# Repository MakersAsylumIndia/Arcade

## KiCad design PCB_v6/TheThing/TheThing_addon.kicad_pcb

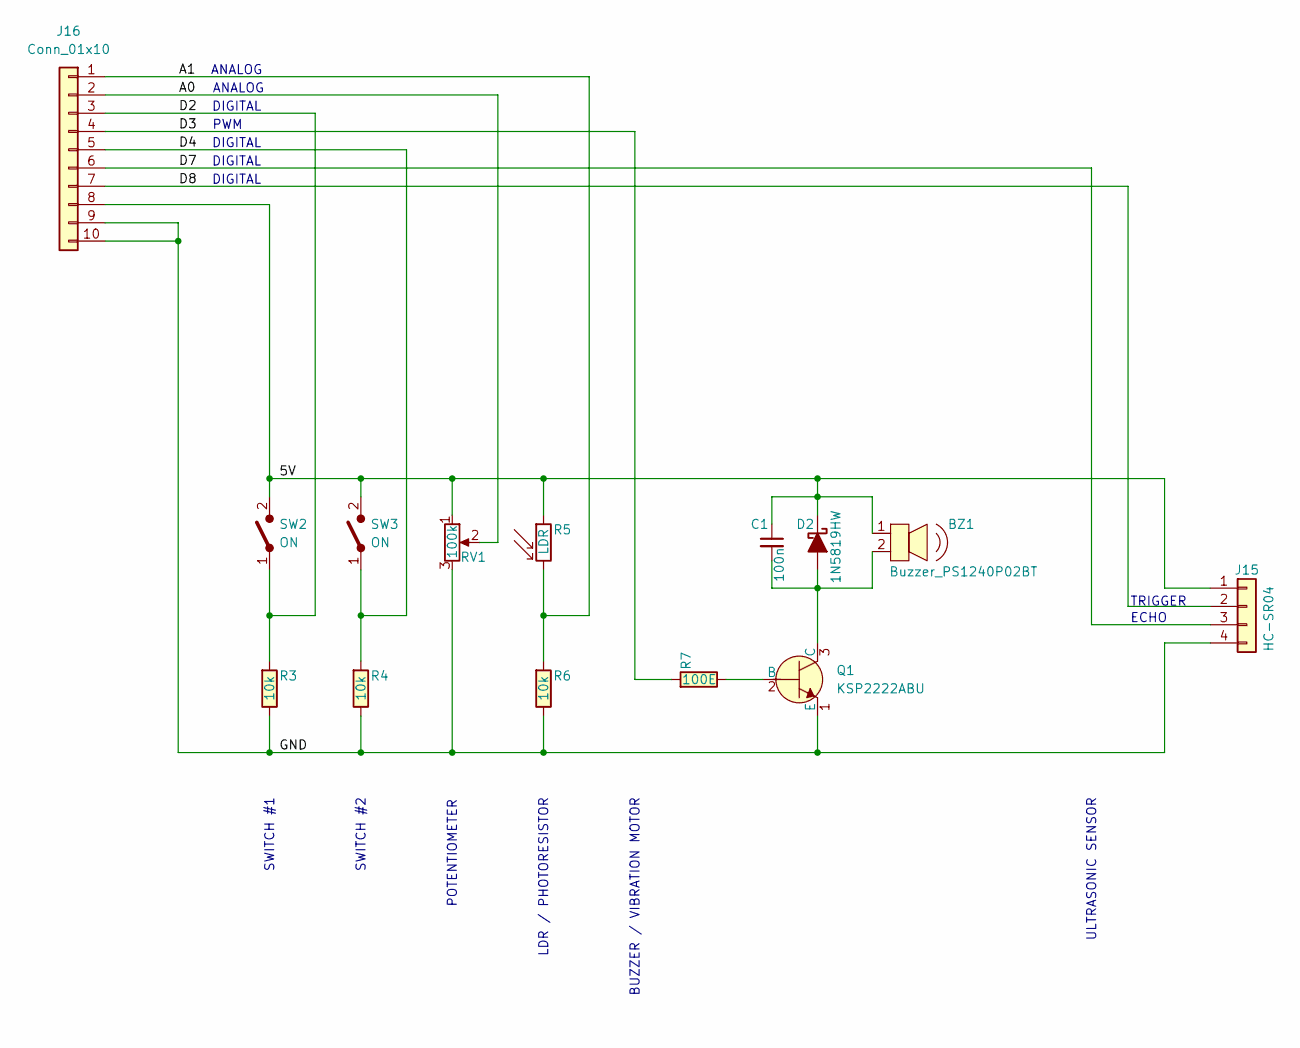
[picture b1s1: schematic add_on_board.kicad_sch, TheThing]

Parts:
BZ1: Buzzer_PS1240P02BT; Buzzer_12x9.5RM7.6; MPN PS1240P02BT; Digi-Key_PN 445-2525-1-ND
C1: 100n; C_Disc_D3.0mm_W2.0mm_P2.50mm
D2: 1N5819HW; D_DO-41_SOD81_P10.16mm_Horizontal
J15: HC-SR04; PinSocket_1x04_P2.54mm_Vertical
J16: Conn_01x10; PinHeader_1x10_P2.54mm_Vertical
Q1: KSP2222ABU; TO-92_HandSolder; MPN KSP2222ABU; Digi-Key_PN KSP2222ABUFS-ND
R3, R4, R6: 10k; R_Axial_DIN0207_L6.3mm_D2.5mm_P7.62mm_Horizontal
R5: LDR; R_LDR_4.9x4.2mm_P2.54mm_Vertical
R7: 100E; R_Axial_DIN0207_L6.3mm_D2.5mm_P7.62mm_Horizontal
RV1: 100k; TRIM_3352T-1-253LF
SW2, SW3: ON; SWITCH_PUSH_6mm_12mm

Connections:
/Add_on_Board/5V: BZ1.1, C1.1, D2.1 (K), J15.1, J16.8, R5.1, RV1.1, SW2.2 (B), SW3.2 (B)
/Add_on_Board/A0: J16.2, RV1.2
/Add_on_Board/A1: J16.1, R5.2, R6.1
/Add_on_Board/D2: J16.3, R3.1, SW2.1 (A)
/Add_on_Board/D3: J16.4, R7.1
/Add_on_Board/D4: J16.5, R4.1, SW3.1 (A)
/Add_on_Board/D7: J15.3, J16.6
/Add_on_Board/D8: J15.2, J16.7
/Add_on_Board/GND: J15.4, J16.9, J16.10, Q1.1 (E), R3.2, R4.2, R6.2, RV1.3
unnamed: BZ1.2, C1.2, D2.2 (A), Q1.3 (C)
unnamed: Q1.2 (B), R7.2

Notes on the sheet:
SWITCH #1
BUZZER / VIBRATION MOTOR
SWITCH #2
ULTRASONIC SENSOR
ANALOG
DIGITAL
PWM
LDR / PHOTORESISTOR
ECHO
TRIGGER
POTENTIOMETER

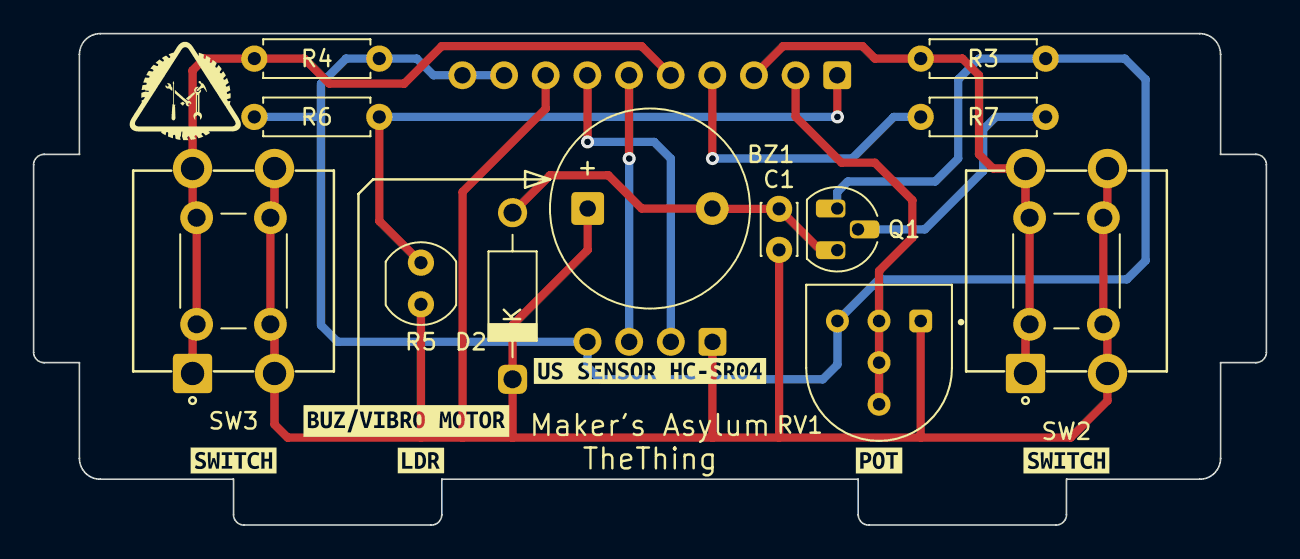
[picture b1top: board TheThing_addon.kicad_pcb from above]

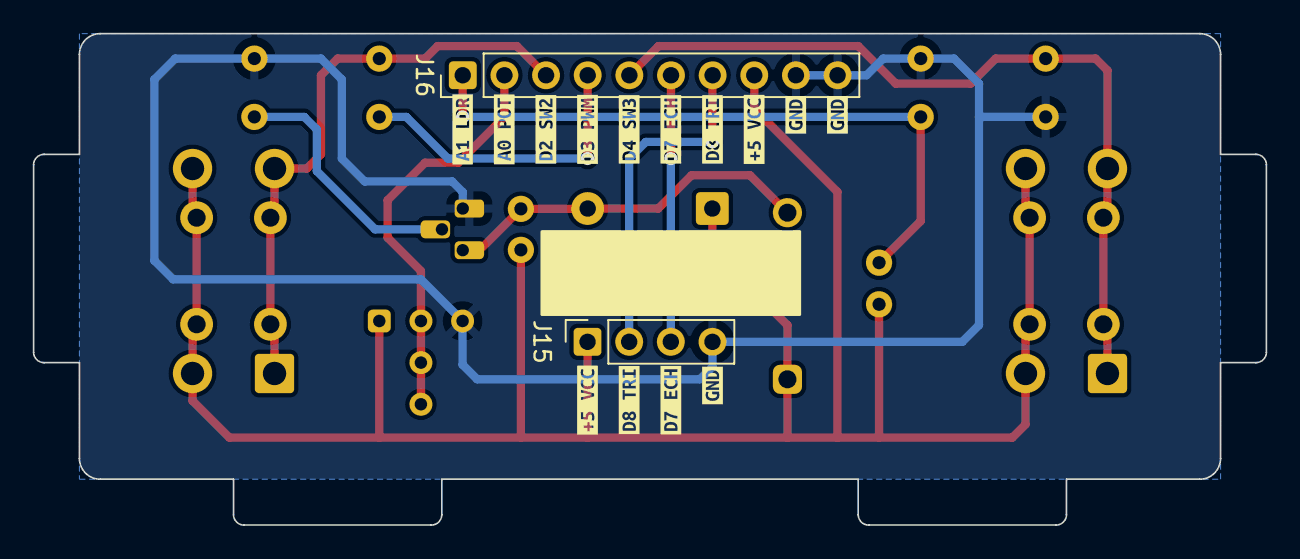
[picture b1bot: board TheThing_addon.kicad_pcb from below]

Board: 2 copper layers, 75.2 x 30.0 mm, 34 parts (16 on the bottom side), 11 nets.

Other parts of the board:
kibuzzard-67A11ADA: G***; kibuzzard-67A11ADA
kibuzzard-67A22DCA: G***; kibuzzard-67A22DCA
kibuzzard-67A22DD3: G***; kibuzzard-67A22DD3
kibuzzard-67A22DDD: G***; kibuzzard-67A22DDD
kibuzzard-67A22DE4: G***; kibuzzard-67A22DE4
kibuzzard-67A22DF7: G***; kibuzzard-67A22DF7
kibuzzard-67A22E24: G***; kibuzzard-67A22E24
kibuzzard-67A121CB: G***; kibuzzard-67A121CB
kibuzzard-67A121DF: G***; kibuzzard-67A121DF
kibuzzard-67A121F4: G***; kibuzzard-67A121F4
kibuzzard-67A122A3, kibuzzard-67A122A3#2: G***; kibuzzard-67A122A3
kibuzzard-67A122B8: G***; kibuzzard-67A122B8
kibuzzard-67A122C1, kibuzzard-67A122C1#2: G***; kibuzzard-67A122C1
kibuzzard-67A201C7: G***; kibuzzard-67A201C7
kibuzzard-67A201D4: G***; kibuzzard-67A201D4
kibuzzard-67A1228F: G***; kibuzzard-67A1228F
kibuzzard-67A12228: G***; kibuzzard-67A12228
kibuzzard-67A12264: G***; kibuzzard-67A12264

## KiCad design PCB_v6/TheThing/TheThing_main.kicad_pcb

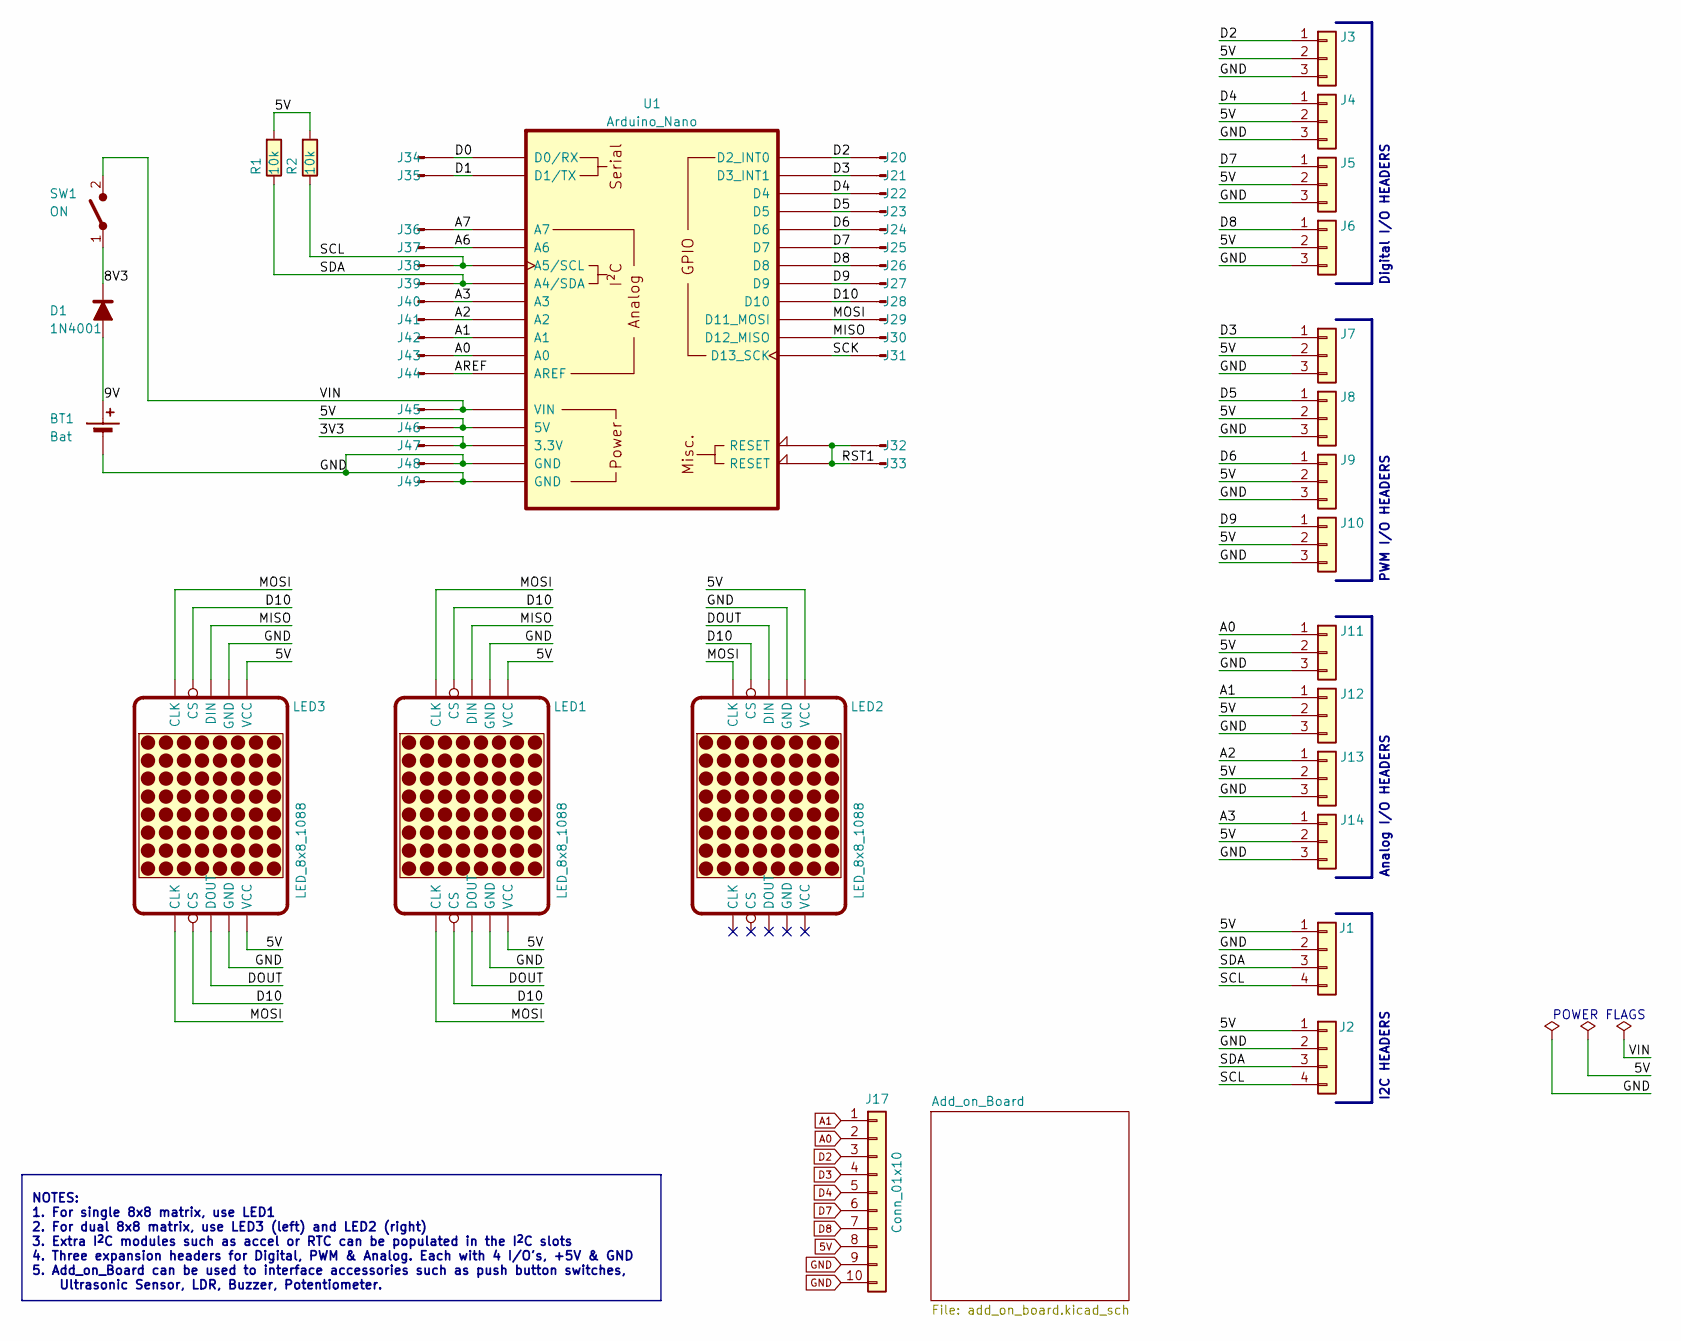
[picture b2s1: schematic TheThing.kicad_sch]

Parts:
BT1: Bat; PinHeader_1x02_P2.54mm_Vertical
D1: 1N4001; D_DO-41_SOD81_P10.16mm_Horizontal
J1, J2: Conn_I2C; PinHeader_1x04_P2.54mm_Vertical
J3, J4, J5, J6, J7, J8, J9, J10, J11, J12, J13, J14: Conn_01x03; PinHeader_1x03_P2.54mm_Vertical
J17: Conn_01x10; PinHeader_1x10_P2.54mm_Vertical
J20: D2; PinHeader_1x01_P2.54mm_Vertical
J21: D3; PinHeader_1x01_P2.54mm_Vertical
J22: D4; PinHeader_1x01_P2.54mm_Vertical
J23: D5; PinHeader_1x01_P2.54mm_Vertical
J24: D6; PinHeader_1x01_P2.54mm_Vertical
J25: D7; PinHeader_1x01_P2.54mm_Vertical
J26: D8; PinHeader_1x01_P2.54mm_Vertical
J27: D9; PinHeader_1x01_P2.54mm_Vertical
J28: D10; PinHeader_1x01_P2.54mm_Vertical
J29: D11; PinHeader_1x01_P2.54mm_Vertical
J30: D12; PinHeader_1x01_P2.54mm_Vertical
J31: D13; PinHeader_1x01_P2.54mm_Vertical
J32, J33: RST1; PinHeader_1x01_P2.54mm_Vertical
J34: D0; PinHeader_1x01_P2.54mm_Vertical
J35: D1; PinHeader_1x01_P2.54mm_Vertical
J36: A7; PinHeader_1x01_P2.54mm_Vertical
J37: A6; PinHeader_1x01_P2.54mm_Vertical
J38: A5; PinHeader_1x01_P2.54mm_Vertical
J39: A4; PinHeader_1x01_P2.54mm_Vertical
J40: A3; PinHeader_1x01_P2.54mm_Vertical
J41: A2; PinHeader_1x01_P2.54mm_Vertical
J42: A1; PinHeader_1x01_P2.54mm_Vertical
J43: A0; PinHeader_1x01_P2.54mm_Vertical
J44: AREF; PinHeader_1x01_P2.54mm_Vertical
J45: VIN; PinHeader_1x01_P2.54mm_Vertical
J46: 5V; PinHeader_1x01_P2.54mm_Vertical
J47: 3V3; PinHeader_1x01_P2.54mm_Vertical
J48: GND1; PinHeader_1x01_P2.54mm_Vertical
J49: GND2; PinHeader_1x01_P2.54mm_Vertical
LED1, LED2, LED3: LED_8x8_1088; LED_matrix_8x8_M1088
R1, R2: 10k; R_Axial_DIN0207_L6.3mm_D2.5mm_P7.62mm_Horizontal
SW1: ON; SW_CuK_OS102011MA1QN1_SPDT_Angled
U1: Arduino_Nano; Arduino_Nano_v2_NoSPI

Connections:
5V: J1.1, J2.1, J3.2, J4.2, J5.2, J6.2, J7.2, J8.2, J9.2, J10.2, J11.2, J12.2, J13.2, J14.2, J17.8, J46.1, LED1.VCC1 (VCC), LED1.VCC2 (VCC), LED2.VCC1 (VCC), LED3.VCC1 (VCC), LED3.VCC2 (VCC), R1.1, R2.1, U1.5V
/3V3: J47.1, U1.3V3 (3.3V)
/8V3: D1.1 (K), SW1.1 (A)
/9V: BT1.1 (+), D1.2 (A)
/A2: J13.1, J41.1, U1.A2
/A3: J14.1, J40.1, U1.A3
/A6: J37.1, U1.A6
/A7: J36.1, U1.A7
/AREF: J44.1, U1.AREF
/D0: J34.1, U1.D0 (D0/RX)
/D1: J35.1, U1.D1 (D1/TX)
/D5: J8.1, J23.1, U1.D5
/D6: J9.1, J24.1, U1.D6
/D9: J10.1, J27.1, U1.D9
/D10: J28.1, LED1.CS1 (CS), LED1.CS2 (CS), LED2.CS1 (CS), LED3.CS1 (CS), LED3.CS2 (CS), U1.D10
/DOUT: LED1.DOUT, LED2.DIN, LED3.DOUT
/MISO: J30.1, LED1.DIN, LED3.DIN, U1.D12 (D12_MISO)
/MOSI: J29.1, LED1.CLK1 (CLK), LED1.CLK2 (CLK), LED2.CLK1 (CLK), LED3.CLK1 (CLK), LED3.CLK2 (CLK), U1.D11 (D11_MOSI)
/RST1: J32.1, J33.1, U1.RST1 (RESET), U1.RST2 (RESET)
/SCK: J31.1, U1.D13 (D13_SCK)
/SCL: J1.4, J2.4, J38.1, R2.2, U1.A5 (A5/SCL)
/SDA: J1.3, J2.3, J39.1, R1.2, U1.A4 (A4/SDA)
/VIN: J45.1, SW1.2 (B), U1.VIN
A0: J11.1, J17.2, J43.1, U1.A0
A1: J12.1, J17.1, J42.1, U1.A1
D2: J3.1, J17.3, J20.1, U1.D2 (D2_INT0)
D3: J7.1, J17.4, J21.1, U1.D3 (D3_INT1)
D4: J4.1, J17.5, J22.1, U1.D4
D7: J5.1, J17.6, J25.1, U1.D7
D8: J6.1, J17.7, J26.1, U1.D8
GND: BT1.2 (-), J1.2, J2.2, J3.3, J4.3, J5.3, J6.3, J7.3, J8.3, J9.3, J10.3, J11.3, J12.3, J13.3, J14.3, J17.9, J17.10, J48.1, J49.1, LED1.GND1 (GND), LED1.GND2 (GND), LED2.GND1 (GND), LED3.GND1 (GND), LED3.GND2 (GND), U1.GND1 (GND), U1.GND2 (GND)

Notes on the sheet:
Digital I/O HEADERS
I2C HEADERS
POWER FLAGS
NOTES: 1. For single 8x8 matrix, use LED1 2. For dual 8x8 matrix, use LED3 (left) and LED2 (right) 3. Extra I^{2}C modules such as accel or RTC can be populated in the I^{2}C slots 4. Three expansion headers for Digital, PWM & Analog. Each with 4 I/O's, +5V & GND 5. Add_on_Board can be used to inte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
PWM I/O HEADERS
Analog I/O HEADERS

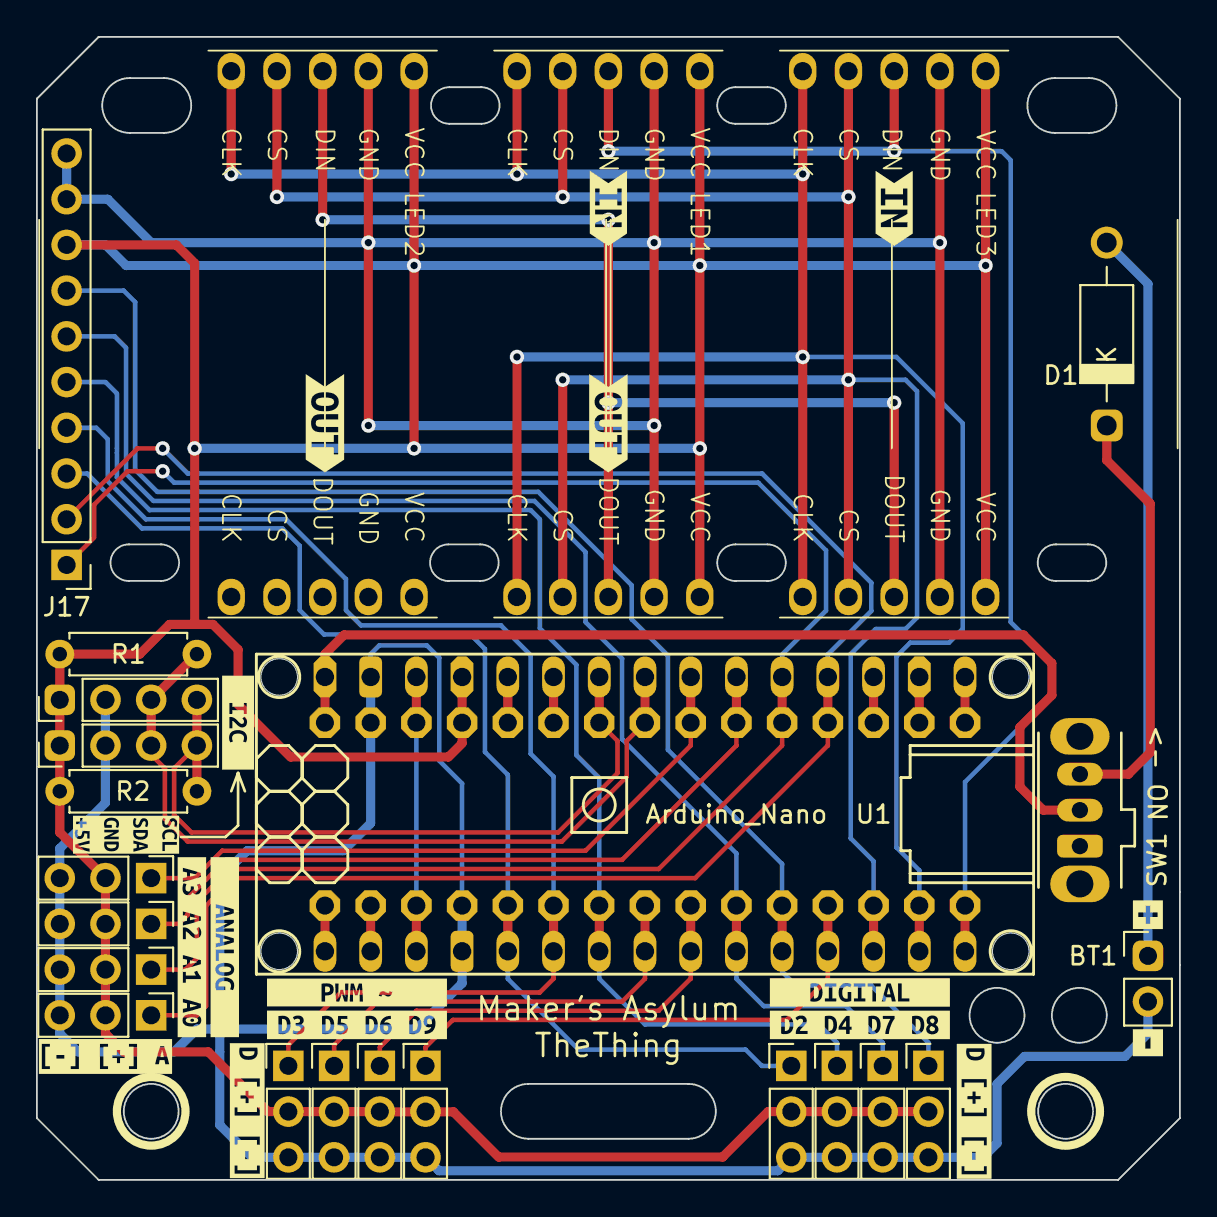
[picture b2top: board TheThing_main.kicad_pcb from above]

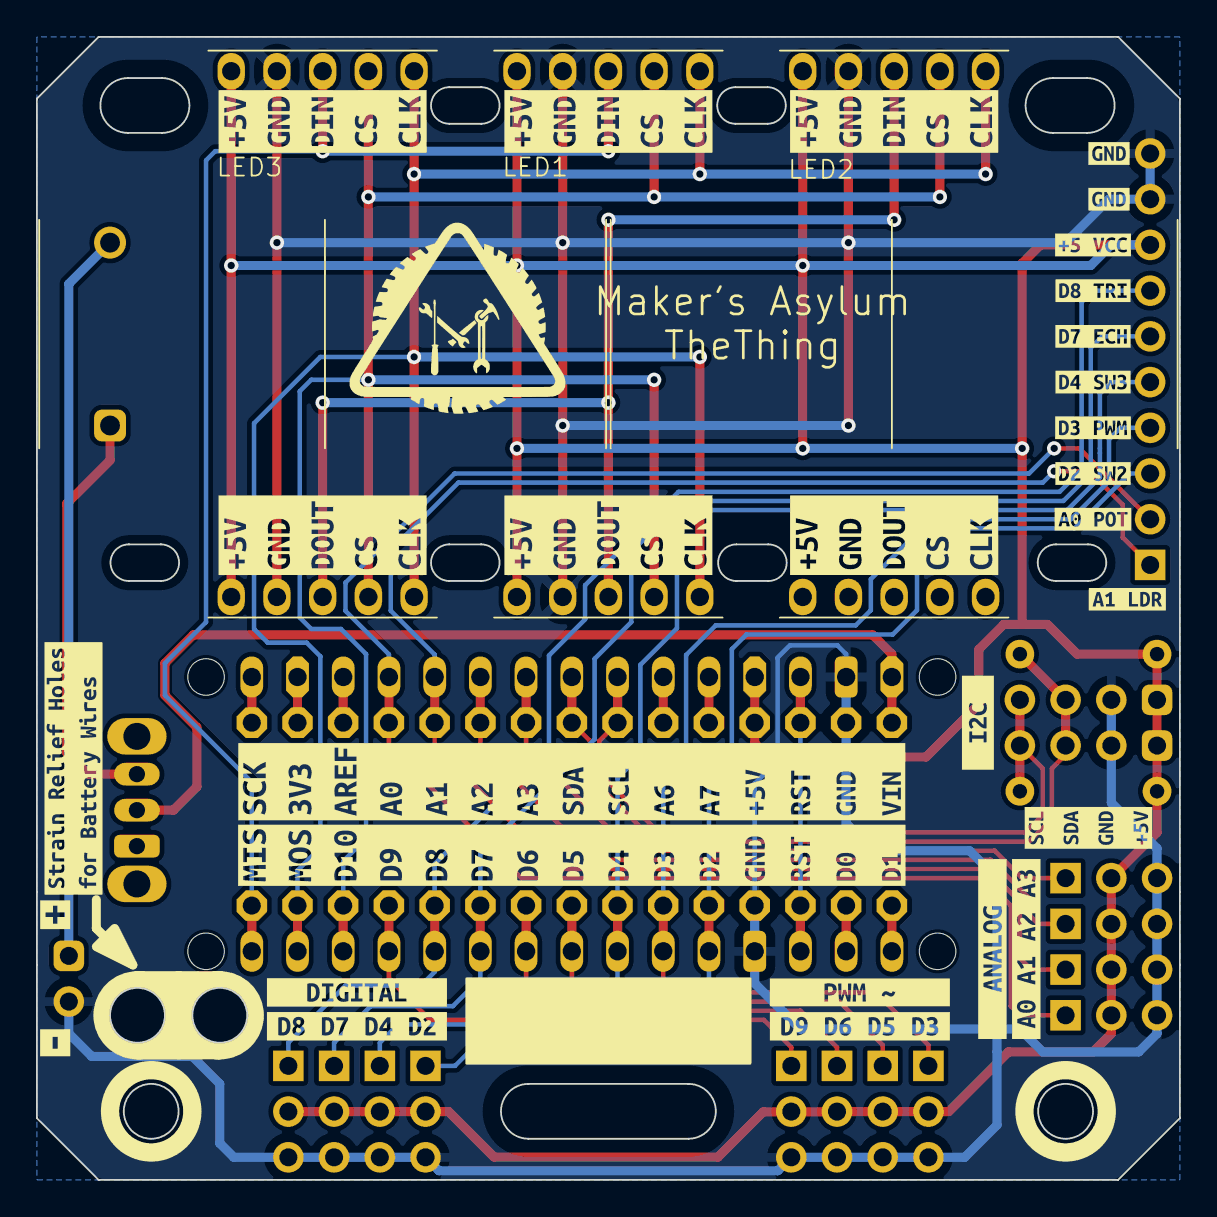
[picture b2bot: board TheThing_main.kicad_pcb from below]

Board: 2 copper layers, 63.5 x 63.5 mm, 100 parts (29 on the bottom side), 31 nets.

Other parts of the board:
kibuzzard-67A1FC5E: G***; kibuzzard-67A1FC5E
kibuzzard-67A1FC23: G***; kibuzzard-67A1FC23
kibuzzard-67A1FC29: G***; kibuzzard-67A1FC29
kibuzzard-67A1FC51: G***; kibuzzard-67A1FC51
kibuzzard-67A1FCC2: G***; kibuzzard-67A1FCC2
kibuzzard-67A1FCF1: G***; kibuzzard-67A1FCF1
kibuzzard-67A1FD26: G***; kibuzzard-67A1FD26
kibuzzard-67A11ADA: G***; kibuzzard-67A11ADA
kibuzzard-67A121CB: G***; kibuzzard-67A121CB
kibuzzard-67A121DF: G***; kibuzzard-67A121DF
kibuzzard-67A121F4: G***; kibuzzard-67A121F4
kibuzzard-67A122A3: G***; kibuzzard-67A122A3
kibuzzard-67A122B8: G***; kibuzzard-67A122B8
kibuzzard-67A122C1: G***; kibuzzard-67A122C1
kibuzzard-67A201FA: G***; kibuzzard-67A201FA
kibuzzard-67A1228F: G***; kibuzzard-67A1228F
kibuzzard-67A2022B: G***; kibuzzard-67A2022B
kibuzzard-67A2040F: G***; kibuzzard-67A2040F
kibuzzard-67A2291F: G***; kibuzzard-67A2291F
kibuzzard-67A10623: G***; kibuzzard-67A10623
kibuzzard-67A11942: G***; kibuzzard-67A11942
kibuzzard-67A12228: G***; kibuzzard-67A12228
kibuzzard-67A12264: G***; kibuzzard-67A12264
kibuzzard-67A20214: G***; kibuzzard-67A20214
kibuzzard-67A20238: G***; kibuzzard-67A20238
kibuzzard-67A20268: G***; kibuzzard-67A20268
kibuzzard-67A20273: G***; kibuzzard-67A20273
kibuzzard-67A20403: G***; kibuzzard-67A20403
kibuzzard-67A20417: G***; kibuzzard-67A20417
kibuzzard-67A20431: G***; kibuzzard-67A20431
kibuzzard-67A20463: G***; kibuzzard-67A20463
kibuzzard-67A20470: G***; kibuzzard-67A20470
kibuzzard-67A22935: G***; kibuzzard-67A22935
kibuzzard-6461CA59, kibuzzard-6461CA59#2: G***; kibuzzard-6461CA59
kibuzzard-6461CA60, kibuzzard-6461CA60#2: G***; kibuzzard-6461CA60
kibuzzard-6640C3B8, kibuzzard-6640C3B8#2: G***; kibuzzard-6640C3B8
kibuzzard-64612FA6, kibuzzard-64612FA6#2: G***; kibuzzard-64612FA6
kibuzzard-64612FED, kibuzzard-64612FED#2: G***; kibuzzard-64612FED
kibuzzard-66412AF8: G***; kibuzzard-66412AF8
kibuzzard-6461376B: G***; kibuzzard-6461376B
kibuzzard-6461377A: G***; kibuzzard-6461377A

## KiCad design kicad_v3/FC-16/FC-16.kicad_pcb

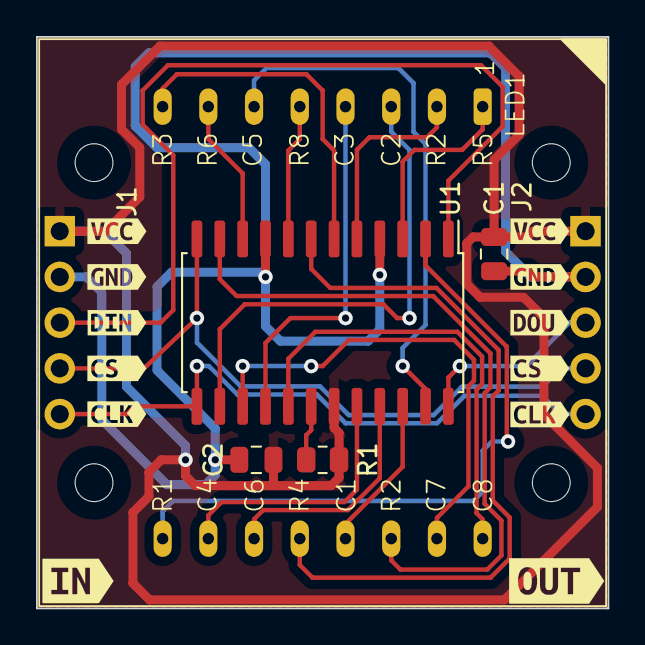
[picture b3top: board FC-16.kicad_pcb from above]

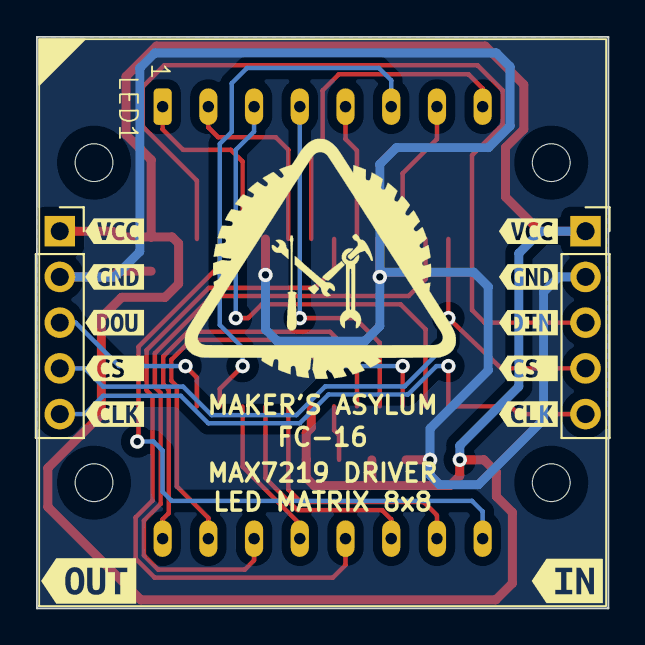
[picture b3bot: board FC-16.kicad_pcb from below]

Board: 2 copper layers, 31.8 x 31.8 mm, 35 parts (14 on the bottom side), 23 nets.

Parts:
C1: 10uF; C_0805_2012Metric
C2: 100nF; C_0805_2012Metric
H1, H2, H3, H4: MountingHole; MountingHole_2.1mm
J1: DIN; PinSocket_1x05_P2.54mm_Vertical
J2: DOUT; PinSocket_1x05_P2.54mm_Vertical
LED1: 1088AS; 8x8_LED_M1088ASR
R1: 47k; R_0805_2012Metric
U1: MAX7221xWG; SOIC-24W_7.5x15.4mm_P1.27mm
kibuzzard-6458BD8D: G***; kibuzzard-6458BD8D
kibuzzard-6458BD81: G***; kibuzzard-6458BD81
kibuzzard-6458C0A5: G***; kibuzzard-6458C0A5
kibuzzard-6458C1A5: G***; kibuzzard-6458C1A5
kibuzzard-6458C1BA: G***; kibuzzard-6458C1BA
kibuzzard-6458C1CB: G***; kibuzzard-6458C1CB
kibuzzard-6458C1D4: G***; kibuzzard-6458C1D4
kibuzzard-6458C1DE: G***; kibuzzard-6458C1DE
kibuzzard-6458C1E6: G***; kibuzzard-6458C1E6
kibuzzard-6458C1EF: G***; kibuzzard-6458C1EF
kibuzzard-6458C1F6: G***; kibuzzard-6458C1F6
kibuzzard-6458C1FE: G***; kibuzzard-6458C1FE
kibuzzard-6458C03B: G***; kibuzzard-6458C03B
kibuzzard-6458C07B: G***; kibuzzard-6458C07B
kibuzzard-6458C08C: G***; kibuzzard-6458C08C
kibuzzard-6458C09F: G***; kibuzzard-6458C09F
kibuzzard-6458C17F: G***; kibuzzard-6458C17F
kibuzzard-6458C067: G***; kibuzzard-6458C067
kibuzzard-6458C074: G***; kibuzzard-6458C074
kibuzzard-6458C083: G***; kibuzzard-6458C083
kibuzzard-6458C092: G***; kibuzzard-6458C092
kibuzzard-6458C097: G***; kibuzzard-6458C097
kibuzzard-6458C190: G***; kibuzzard-6458C190
kibuzzard-6458C228: G***; kibuzzard-6458C228

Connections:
/CLK: J1.5, J2.5, U1.13 (CLK)
/CS: J1.4, J2.4, U1.12 (~CS)
/DIN: J1.3, U1.1 (DIN)
/DOUT: J2.3, U1.24 (DOUT)
/GND: C1.2, C2.2, J1.2, J2.2, U1.4 (GND), U1.9 (GND)
/ISET: R1.2, U1.18 (ISET)
/VCC: C1.1, C2.1, J1.1, J2.1, R1.1, U1.19 (V+)
unnamed: LED1.13 (C1), U1.22 (SEG_DP)
unnamed: LED1.3 (C2), U1.14 (SEG_A)
unnamed: LED1.4 (C3), U1.16 (SEG_B)
unnamed: LED1.10 (C4), U1.20 (SEG_C)
unnamed: LED1.6 (C5), U1.23 (SEG_D)
unnamed: LED1.11 (C6), U1.21 (SEG_E)
unnamed: LED1.15 (C7), U1.15 (SEG_F)
unnamed: LED1.16 (C8), U1.17 (SEG_G)
unnamed: LED1.9 (R1), U1.2 (DIG_0)
unnamed: LED1.14 (R2), U1.11 (DIG_1)
unnamed: LED1.8 (R3), U1.6 (DIG_2)
unnamed: LED1.12 (R4), U1.7 (DIG_3)
unnamed: LED1.1 (R5), U1.3 (DIG_4)
unnamed: LED1.7 (R6), U1.10 (DIG_5)
unnamed: LED1.2 (R7), U1.5 (DIG_6)
unnamed: LED1.5 (R8), U1.8 (DIG_7)
